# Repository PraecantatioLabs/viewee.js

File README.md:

# viewee.js

ViewEE is a software to view PCB layouts in various formats. Currently supported are Cadsoft Eagle `.brd`
, Kicad `.kicad_pcb` and gEDA `.pcb` formats.

[More information](http://cuwire.io/viewee/)

### Issues

Parser and renderer are not ideal. Some problems can be fixed (pad, via shapes),
some — not (I don't have an access to the eagle font). At current stage you will
definitely face problem with thru hole pad shapes, arcs, rotated elements and text.
Eagle parser have best quality, Kicad renders ok and gEDA pcb parser is quite basic.

### Limitations

Currently only 2layer boards are supported.

### Reference rendering in version 0.2.0, [current version](http://cuwire.io/viewee/preview/) is much better.

### Mac OS X QuickLook plugin

You can install preview version of ViewEE for Mac OS X by downloading QuickLook plugin
from [releases page](https://github.com/cuwire/viewee.js/releases).

Download, unarchive, copy `.qlgenerator` file to the `~/Library/QuickLook/` folder.

#### Video

<div class="videoWrapper ViewEE-QuickLook">
    <!-- Copy & Pasted from YouTube -->
    <iframe width="100%" height="315" src="https://www.youtube.com/embed/ihnCz3UOc7Y" frameborder="0" allowfullscreen></iframe>
</div>

### Library

Also you can use a javascript parser and renderer on your own page. Here is [an example](/viewee/preview/) and [repository](https://github.com/cuwire/viewee.js).

## Thanks

Huge thanks to people who created the original version
for [Eagle board viewer](https://github.com/presseverykey/everywhere-eagle-viewer)
and inspired me to [fix some bugs](https://github.com/presseverykey/everywhere-eagle-viewer/issues/3) and create derived software.

Rendering test with [BrowserStack](https://browserstack.com)

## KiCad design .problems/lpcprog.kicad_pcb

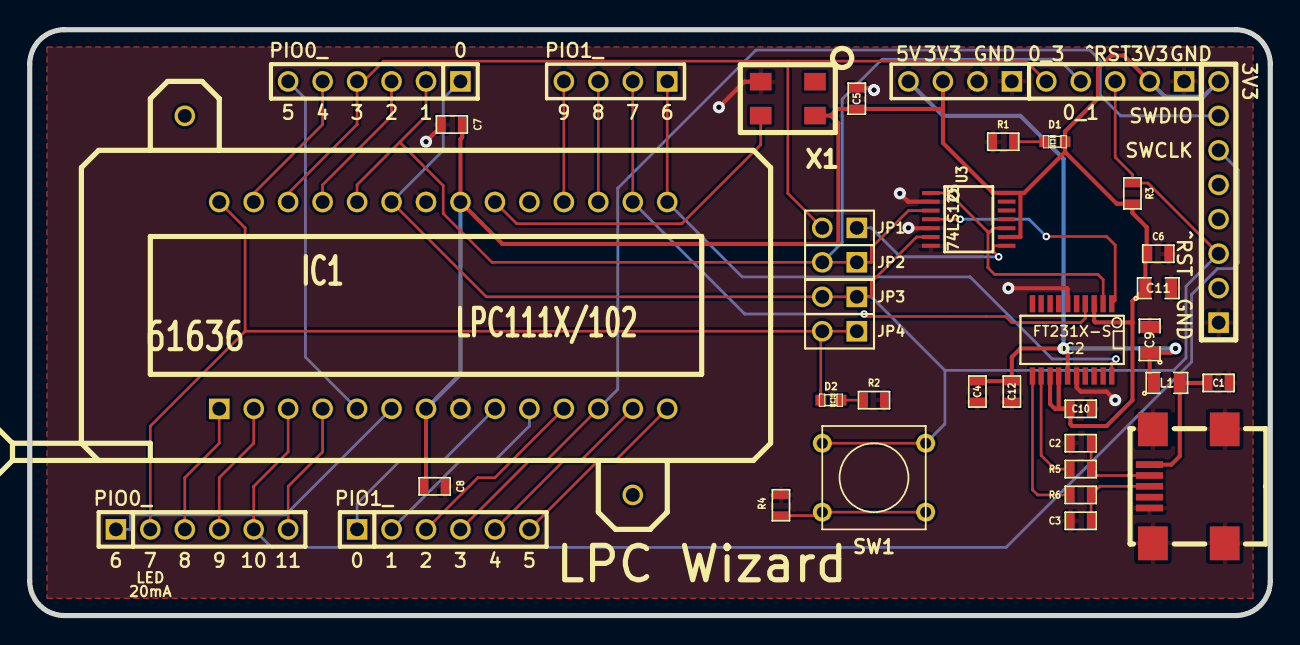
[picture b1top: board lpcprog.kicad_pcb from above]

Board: 2 copper layers, 91.4 x 43.2 mm, 38 parts (0 on the bottom side), 37 nets.

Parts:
C1: 10nF; SM0603_Capa
C2, C3: 47pF; SM0603_Capa
C4, C5, C6, C7, C8, C10, C12: 0.1uF; SM0603_Capa
C9, C11: 4.7uF; SM0805
D1, D2: LED; LED-0603
IC1: LPC111X/102; 28tex600
IC2: FT231X-S; SSOP20
J2: MINI-USB-SHLD; MINI-USB-UX60A-MB-5ST
JP1, JP2, JP3, JP4: JUMPER; PIN_ARRAY_2X1
L1: INDUCTOR; SM0805
P1, P2, P3: CONN_6; PIN_ARRAY-6X1
P4, P5: CONN_4; PIN_ARRAY_4x1
P6: CONN_8; pin_array_8x1
P7: CONN_5; PIN_ARRAY_5x1
R1, R2: 220R; SM0603
R3: 10K; SM0603
R4: 100R; SM0603
R5, R6: 27R; SM0603
SW1: SW_PUSH; SW_PUSH_SMALL
U3: 74LS125; TSSOP14
X1: CONN_4; OSCILLATOR-FOX924

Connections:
+3.3V: C5.1, C6.1, C7.1, C8.1, C10.1, C11.1, D1.1, IC1.7, IC1.21, IC2.3, IC2.13, IC2.14, P5.3, P6.8, P7.2, R3.1, U3.9, U3.14, X1.4
+5V: C4.1, C9.1, C12.2, IC2.15, L1.1, P5.4
/BOOT: IC1.24, JP2.1, JP2.2, P1.2, P7.4, U3.3
/DTR: IC2.1, U3.4
/LED: D2.1, IC1.28, JP4.1, JP4.2, P2.2
/PIO0_0: IC1.23, JP3.1, JP3.2, P1.1, P6.3, P7.3, R3.2, SW1.1, U3.6
/PIO0_2: IC1.25, P1.3
/PIO0_3: IC1.26, JP1.2, P1.4, P7.5
/PIO0_4: IC1.27, P1.5
/PIO0_5: IC1.5, P1.6
/PIO0_6: IC1.6, P2.1
/PIO0_8: IC1.1, P2.3
/PIO0_9: IC1.2, P2.4
/PIO0_10: IC1.3, P2.5, P6.6
/PIO0_11: IC1.4, P2.6
/PIO1_0: IC1.9, P3.1
/PIO1_1: IC1.10, P3.2
/PIO1_2: IC1.11, P3.3
/PIO1_3: IC1.12, P3.4, P6.7
/PIO1_4: IC1.13, P3.5
/PIO1_5: IC1.14, P3.6
/PIO1_6: IC1.15, IC2.20, P4.1
/PIO1_7: IC1.16, IC2.4, P4.2
/PIO1_8: IC1.17, P4.3
/PIO1_9: IC1.18, P4.4
/RTS: IC2.2, U3.1, U3.10
/USBDM: IC2.12, R5.2
/USBDP: IC2.11, R6.2
GND: C1.1, C2.2, C3.2, C4.2, C5.2, C6.2, C7.2, C8.2, C9.2, C10.2, C11.2, C12.1, IC1.8, IC1.22, IC2.6, IC2.16, J2.5, J2.6, P5.1, P5.2, P6.1, P7.1, R1.2, R2.2, R4.2, U3.2, U3.5, U3.7, X1.2
unnamed: R4.1, SW1.2
unnamed: JP1.1, U3.8
unnamed: IC1.20, X1.3
unnamed: D1.2, R1.1
unnamed: D2.2, R2.1
unnamed: C2.1, J2.2, R5.1
unnamed: C1.2, J2.1, L1.2
unnamed: C3.1, J2.3, R6.1

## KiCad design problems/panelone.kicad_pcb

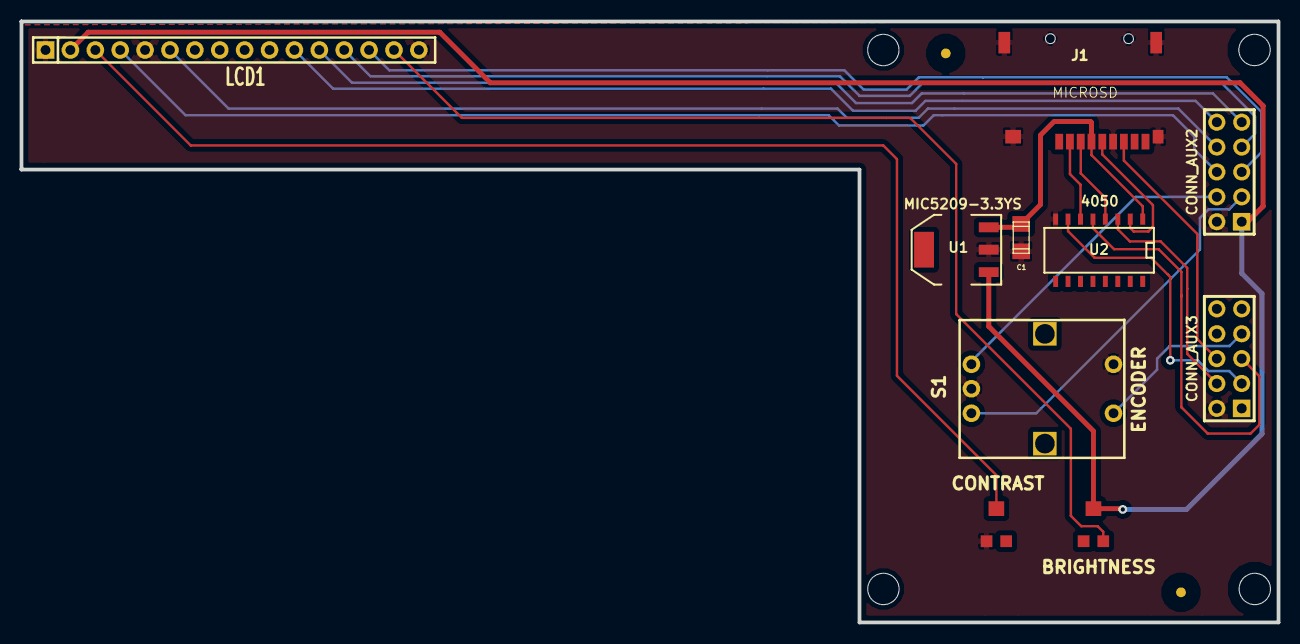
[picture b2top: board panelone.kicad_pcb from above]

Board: 2 copper layers, 128.3 x 61.3 mm, 12 parts (0 on the bottom side), 21 nets.

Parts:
C1: 2.2uF; c_1206
Fid1: FID1; Fiducial
Fid2: FID2; Fiducial
J1: MICROSD; MICRO_SD
LCD1: LCD_2X16_SIL; LCD_2004
P1: CONN_AUX3; PIN_ARRAY_5x2
P2: CONN_AUX2; PIN_ARRAY_5x2
RV1: CONTRAST; TC33X-POT
RV2: BRIGHTNESS; TC33X-POT
S1: ENCODER; ALPS_EC12E2424407
U1: MIC5209-3.3YS; SOT223
U2: 4050; SO16N

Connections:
+3.3V: C1.1, J1.4, U1.3, U2.1
+5V: LCD1.2, P1.8, P2.1, RV2.2, U1.1
/CS: P1.3, U2.7
/DI: P1.5, U2.5
/DO: J1.7, P1.6
/_CLK: J1.5, U2.2
/_CS: J1.2, U2.6
/_DI: J1.3, U2.4
GND: C1.2, J1.6, LCD1.1, LCD1.5, LCD1.16, P1.2, P2.2, RV1.1, S1.2, S1.4, U1.2, U2.8
unnamed: LCD1.4, P2.6
unnamed: LCD1.13, P2.7
unnamed: P1.4, U2.3
unnamed: LCD1.3, RV1.2
unnamed: LCD1.6, P2.8
unnamed: LCD1.12, P2.9
unnamed: LCD1.15, RV2.3
unnamed: P1.7, S1.5
unnamed: P2.3, S1.3
unnamed: P2.4, S1.1
unnamed: LCD1.14, P2.5
unnamed: LCD1.11, P2.10

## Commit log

2015-08-21 fixed for retina canvas
2015-08-21 element’s rects, pads; texts
2015-08-22 now support amd and script tag loading
2015-08-22 cleanup
2015-08-22 use selectors instead of ids
2015-08-22 added support for arcs in wires
2015-08-22 added arc support for signal wires
2015-08-22 added example
2015-08-22 crappy, but displays wires, texts
    …positioning is disaster
2015-08-23 vias added
2015-08-24 inline packages support
2015-08-24 elements support
2015-08-24 load parser by analyzing contents; added a new board to the list
2015-08-24 restored original board
2015-08-24 circles WIP
2015-08-24 drawing arcs
2015-08-24 bbox calculation; onclick support
2015-08-24 circles in packages
2015-08-24 fix for package click
2015-08-25 coordYFlip option
2015-08-25 rotate modules
2015-08-25 module text display
2015-08-25 onclick fix for Y-flipped formats
2015-08-25 added support for polygons
2015-08-25 element description support
2015-08-26 amd wrapper
2015-08-28 parser interface
2015-08-28 using embedded font
2015-08-29 proper font loading; interface changes; light theme by default
2015-08-29 fixed polygon draw
2015-08-29 added support for holes
2015-08-29 fixed issue when callback not defined
2015-08-30 package circles support
2015-08-30 spin rotate parsing
2015-08-30 smd rotation and roundness parsing
2015-08-30 fixed issue if color for layer is not defined; darker outlines
2015-08-30 minor
2015-08-30 kicad text align fix
2015-08-30 use default url from form select
2015-08-30 text align renderer
2015-08-30 additional layers to display
2015-08-30 design rules reading
2015-08-30 proper arc draw
2015-08-30 fixes pad rotation for smd pads
2015-08-31 round smd pads
2015-08-31 issues
2015-08-31 circle shaped smd pads
2015-08-31 some fixes for kicad where pads have no name
2015-09-02 fixed arcs and added dashed lines
2015-09-03 fixed positions for plain wires
2015-09-03 minor rendering issues
2015-09-04 text rotation fix for package’s attrs
2015-09-04 additional layers to show
2015-09-04 pad coords already rotated on kicad
2015-09-05 pkg rectangles
2015-09-05 linecap
2015-09-05 flipText fix for kicad
2015-09-05 annoying shape warnings
2015-09-05 ViewEE interface rewrite, test pcb layouts
2015-09-05 typo fix
2015-09-06 added disabled text reference rendering
2015-09-06 kicad layer fixes
2015-09-06 fixed smd pad rotation
2015-09-06 rendering issue if drill == diameter
2015-09-06 signal layer parsing regardless of names
2015-09-20 use selector or supplied canvas element
2015-09-20 cleanup after font loaded
2015-12-02 now supports touch
2016-02-06 moved eagle xml parser into separate file
2016-02-06 removed parser things
2016-02-07 renderer refactor
    splitted to the basic renderer and canvas primitives renderer
2016-02-08 svg renderer alpha
2016-02-08 need to add interactivity by design
2016-02-08 canvas needed much earlier
2016-02-08 draw/redraw thing
2016-02-09 svg hole shapes
2016-02-09 added viewport to scale easily
2016-02-09 fixes wire width
2016-02-09 kicad 16/32 layer pcb
2016-02-09 fixes for oval and square drills
2016-02-09 reason not to process text node
2016-02-10 use restring settings from design rules
2016-02-10 now text rendering not too bad in svg
2016-02-10 4 significant digits
2016-02-10 svg: board flip and rescale
2016-02-10 multiline kicad strings
2016-02-10 shapes for via and pads
2016-02-11 persist scroll position on zoom
2016-02-11 resize on orientation change
2016-02-11 object.assign shim
2016-02-12 trying to reduce computation complexity by using float.toFixed(4)
2016-02-12 shapes long and oval is done without holes
    commented out for now
2016-02-13 no need to draw again on scale
2016-02-13 added scale, draw and redraw timers
2016-02-13 no need to set style, attributes is already set
2016-02-13 minor style fixes
2016-02-14 added ie font
2016-02-27 added load clabback
2016-02-27 HtmlEl and SvgEl functions
2016-02-27 better warning message
2016-02-27 refactor; events support
2016-02-27 loading animation (partially working)
2016-02-27 class name changed
2016-02-27 support for draw operation cache
2016-02-29 removed html inline event handlers
2016-02-29 added link and project logo
2016-02-29 incomplete geda parser
2016-03-01 files renames
2016-03-01 geda parser enable
2016-03-01 allows local files to be read
2016-03-01 ql update
2016-03-01 added dark logo
2016-03-01 pass proper curve param
2016-03-01 fixed arc parsing
2016-03-01 circles now are circular
2016-03-01 check for signal wires to get board dimensions
2016-03-01 package bbox and node test
2016-03-01 fixed issue with dashed lines
2016-03-01 scrollbars
2016-03-02 use angleForRot
2016-03-07 css rework to allow embed
2016-03-08 github browser
2016-03-08 minor style improvements
2016-03-08 Kicad new layers
2016-03-08 style cleanup
2016-03-08 input placeholder
2016-03-11 loading progress bar and style changes
2016-03-13 fixed translated viewport
2016-03-13 slightly better borders detection
2016-03-14 one more progressbar
2016-03-14 seems like I don’t need to rotate parts at bottom
2016-03-16 better README
2016-03-16 repository search
2016-03-16 supports loading github urls
2016-03-16 canvas scaling fix
2016-03-16 updated ql view
2016-03-16 embedded logo
2016-03-16 optimized logo
2016-03-19 resizable controls
2016-04-20 load something by default
2017-01-02 passing
2017-01-13 cleanup: moved SVG DOM code to the SVG renderer
2017-05-05 BrowserStack testing badge
2017-06-15 [es6] board refactor
2017-11-20 renderer rewrite
2017-11-20 rename; fix for line joins; hole's drill
2017-11-20 more fixes for layers
2017-11-20 fix: filled circle rendering
2017-11-20 backport: round polygons/filled circles
2017-11-20 test: canvas works, but null file produced
2017-11-21 fix: canvas rendering
2017-11-21 minor: file move
2017-11-22 refactor: parser.sourceType, clone layer dicts
2017-11-22 feature: easyeda initial parsing completes
2017-11-22 fix: canvas relocation
2017-11-22 fix: board scale
2017-11-22 feature: pads, smds
2017-11-22 fix: easyeda rendering issues
2017-11-23 refactor: move utility function away
2017-11-23 feature: more shapes for easyeda
2017-11-28 fix: arc rendering issues
2017-11-28 feature: use special fonts
2017-11-28 goldplating: proper scopes
2017-11-29 feature: easyeda polys and arcs
2017-11-29 refactor: removed external dependency
2017-11-29 cleanup: moved samples to the another repo

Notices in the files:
problems/panelone.kicad_pcb:
Licensed under CERN OHW Licence 1.2
